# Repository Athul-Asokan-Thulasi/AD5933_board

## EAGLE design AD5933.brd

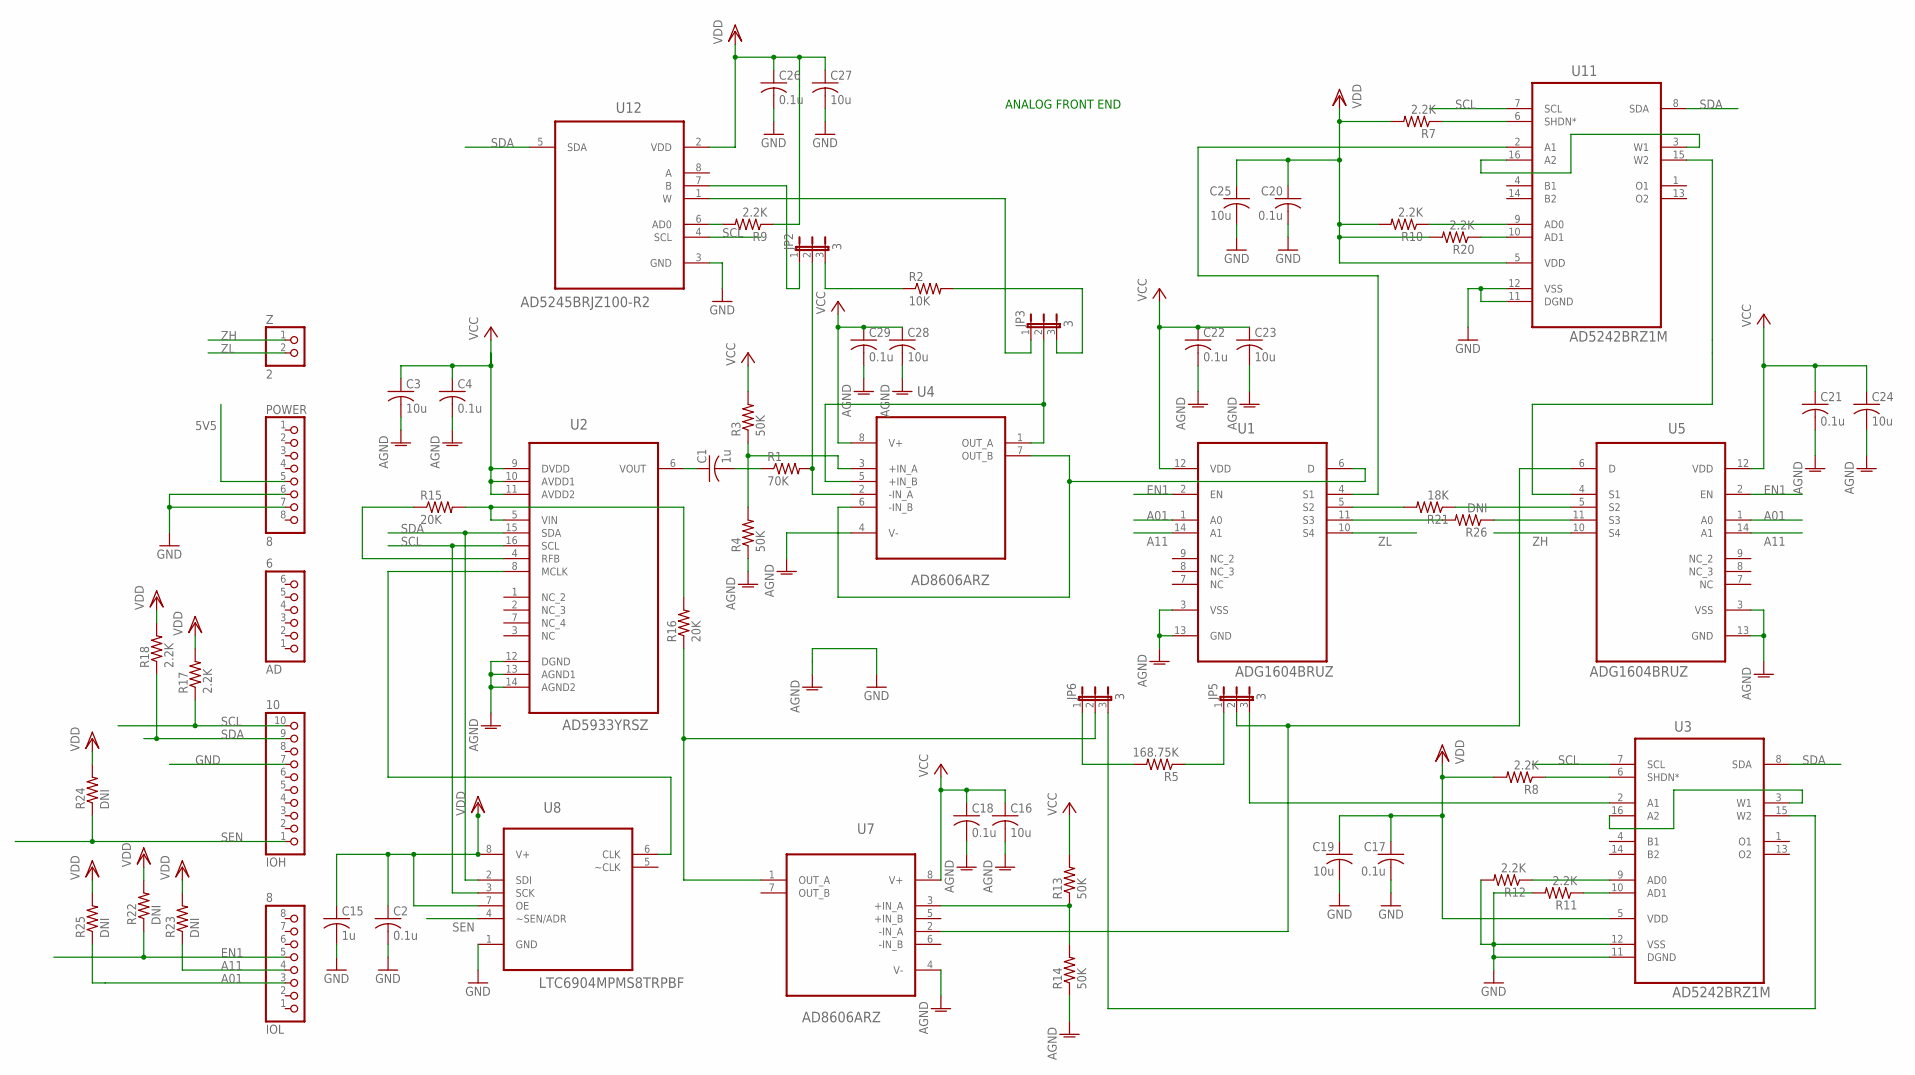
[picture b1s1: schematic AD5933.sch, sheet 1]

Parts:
AD: 6; 1X06
C1, C15: 1u; C0805
C2, C4, C17, C18, C20, C21, C22, C26, C29: 0.1u; C0805
C3, C16, C19, C23, C24, C25, C27, C28: 10u; C0805
IOH: 10; 1X10
IOL: 8; 1X08
JP2, JP3, JP5, JP6: 3; JP2
POWER: 8; 1X08
R1: 70K; M0805
R2: 10K; M0805
R3, R4, R13, R14: 50K; M0805
R5: 168.75K; M0805
R7, R8, R9, R10, R11, R12, R17, R18, R20: 2.2K; M0805
R15, R16: 20K; M0805
R21: 18K; M0805
R22, R23, R24, R25, R26: DNI; M0805
U1, U5: ADG1604BRUZ; SOP65P640X120-14N
U2: AD5933YRSZ; SOP65P640X120-16N
U3, U11: AD5242BRZ1M; SOIC127P600X175-16N
U4, U7: AD8606ARZ; SOIC127P600X175-8N
U8: LTC6904MPMS8TRPBF; SOP65P490X110-8N
U12: AD5245BRJZ100-R2; SOT65P280X145-8N
Z: 2; 1X02

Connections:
5V5: POWER.5; also elsewhere on the board
A01: IOL.3, R25.1, U1.1 (A0), U5.1 (A0)
A11: IOL.4, R23.1, U1.14 (A1), U5.14 (A1)
AGND: C3.2, C4.2, C16.2, C18.2, C21.2, C22.2, C23.2, C24.2, C28.2, C29.2, R4.1, R14.1, U1.3 (VSS), U1.13 (GND), U2.12 (DGND), U2.13 (AGND1), U2.14 (AGND2), U4.4 (V-), U5.3 (VSS), U5.13 (GND), U7.4 (V-); also elsewhere on the board
EN1: IOL.5, R22.1, U1.2 (EN), U5.2 (EN)
GND: C2.2, C15.2, C17.2, C19.2, C20.2, C25.2, C26.2, C27.2, IOH.7, POWER.6, POWER.7, R11.2, R12.2, U3.11 (DGND), U3.12 (VSS), U8.1 (GND), U11.11 (DGND), U11.12 (VSS), U12.3 (GND); also elsewhere on the board
unnamed: C1.1, U2.6 (VOUT)
unnamed: C1.2, R1.1
unnamed: JP5.1, R5.1
unnamed: R7.1, U11.6 (SHDN*)
unnamed: JP3.3, R2.2
unnamed: JP6.1, R5.2
unnamed: R8.1, U3.6 (SHDN*)
unnamed: JP2.3, R2.1
SCL: IOH.10, R17.1, U2.16 (SCL), U3.7 (SCL), U8.3 (SCK), U11.7 (SCL), U12.4 (SCL)
SDA: IOH.9, R18.1, U2.15 (SDA), U3.8 (SDA), U8.2 (SDI), U11.8 (SDA), U12.5 (SDA)
SEN: IOH.1, R24.1, U8.4 (~SEN/ADR)
U1_S1: U1.4 (S1), U11.2 (A1)
U1_S2: R21.2, U1.5 (S2)
U1_S3: R26.2, U1.11 (S3)
U2_MCLK: U2.8 (MCLK), U8.6 (CLK)
U2_RFB: R15.1, U2.4 (RFB)
U2_VIN: R15.2, R16.2, U2.5 (VIN)
U3_A1: JP5.3, U3.2 (A1)
U3_AD0: R12.1, U3.9 (AD0)
U3_AD1: R11.1, U3.10 (AD1)
U3_W1: U3.3 (W1), U3.16 (A2)
U3_W2: JP6.3, U3.15 (W2)
U4_INA++: R3.1, R4.2, U4.3 (+IN_A)
U4_INA--: JP2.2, R1.2, U4.2 (-IN_A)
U4_OUTA: JP3.2, U4.1 (OUT_A), U4.5 (+IN_B)
U4_OUTB: U1.6 (D), U4.6 (-IN_B), U4.7 (OUT_B)
U5_S2: R21.1, U5.5 (S2)
U5_S3: R26.1, U5.11 (S3)
U7_INA+: R13.1, R14.2, U7.3 (+IN_A)
U7_INA-: JP5.2, U5.6 (D), U7.2 (-IN_A)
U7_OUTA: JP6.2, R16.1, U7.1 (OUT_A)
U11_AD0: R10.1, U11.9 (AD0)
U11_AD1: R20.1, U11.10 (AD1)
U11_W1: U11.3 (W1), U11.16 (A2)
U11_W2: U5.4 (S1), U11.15 (W2)
U12_AD0: R9.2, U12.6 (AD0)
U12_B: JP2.1, U12.7 (B)
U12_W: JP3.1, U12.1 (W)
VCC: C3.1, C4.1, C16.1, C18.1, C21.1, C22.1, C23.1, C24.1, C28.1, C29.1, R3.2, R13.2, U1.12 (VDD), U2.9 (DVDD), U2.10 (AVDD1), U2.11 (AVDD2), U4.8 (V+), U5.12 (VDD), U7.8 (V+); also elsewhere on the board
VDD: C2.1, C15.1, C17.1, C19.1, C20.1, C25.1, C26.1, C27.1, R7.2, R8.2, R9.1, R10.2, R17.2, R18.2, R20.2, R22.2, R23.2, R24.2, R25.2, U3.5 (VDD), U8.7 (OE), U8.8 (V+), U11.5 (VDD), U12.2 (VDD); also elsewhere on the board
ZH: U5.10 (S4), Z.1
ZL: U1.10 (S4), Z.2

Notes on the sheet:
ANALOG FRONT END

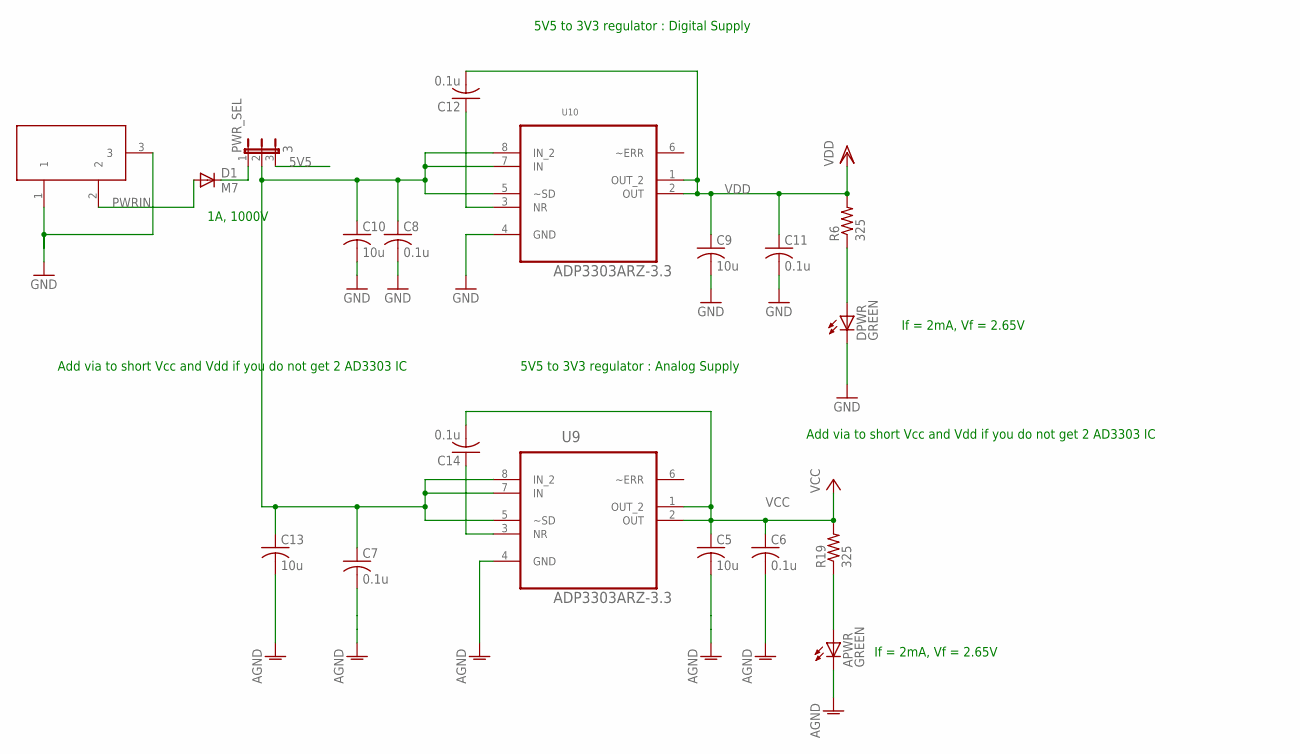
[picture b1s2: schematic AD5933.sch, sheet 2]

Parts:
APWR: GREEN; CHIP-LED0805
C5, C9, C10, C13: 10u; C0805
C6, C7, C8, C11, C12, C14: 0.1u; C0805
D1: M7; SMB
DPWR: GREEN; CHIP-LED0805
PWR_SEL: 3; JP2
R6, R19: 325; M0805
U9, U10: ADP3303ARZ-3.3; SOIC127P600X175-8N
X1: DC21MMX; DC-21MM

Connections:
5V5: PWR_SEL.3; also elsewhere on the board
AGND: APWR.C, C5.2, C6.2, C7.2, C13.2, U9.4 (GND); also elsewhere on the board
GND: C8.2, C9.2, C10.2, C11.2, DPWR.C, U10.4 (GND), X1.1, X1.3; also elsewhere on the board
unnamed: C12.1, U10.3 (NR)
unnamed: DPWR.A, R6.1
unnamed: APWR.A, R19.1
unnamed: C14.1, U9.3 (NR)
PWRIN: D1.A, X1.2
PWR_INPUT: C7.1, C8.1, C10.1, C13.1, PWR_SEL.2, U9.5 (~SD), U9.7 (IN), U9.8 (IN_2), U10.5 (~SD), U10.7 (IN), U10.8 (IN_2)
VCC: C5.1, C6.1, C14.2, R19.2, U9.1 (OUT_2), U9.2 (OUT); also elsewhere on the board
VDD: C9.1, C11.1, C12.2, R6.2, U10.1 (OUT_2), U10.2 (OUT); also elsewhere on the board
VIN: D1.C, PWR_SEL.1

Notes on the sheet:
5V5 to 3V3 regulator : Digital Supply
5V5 to 3V3 regulator : Analog Supply
If = 2mA, Vf = 2.65V
1A, 1000V
Add via to short Vcc and Vdd if you do not get 2 AD3303 IC

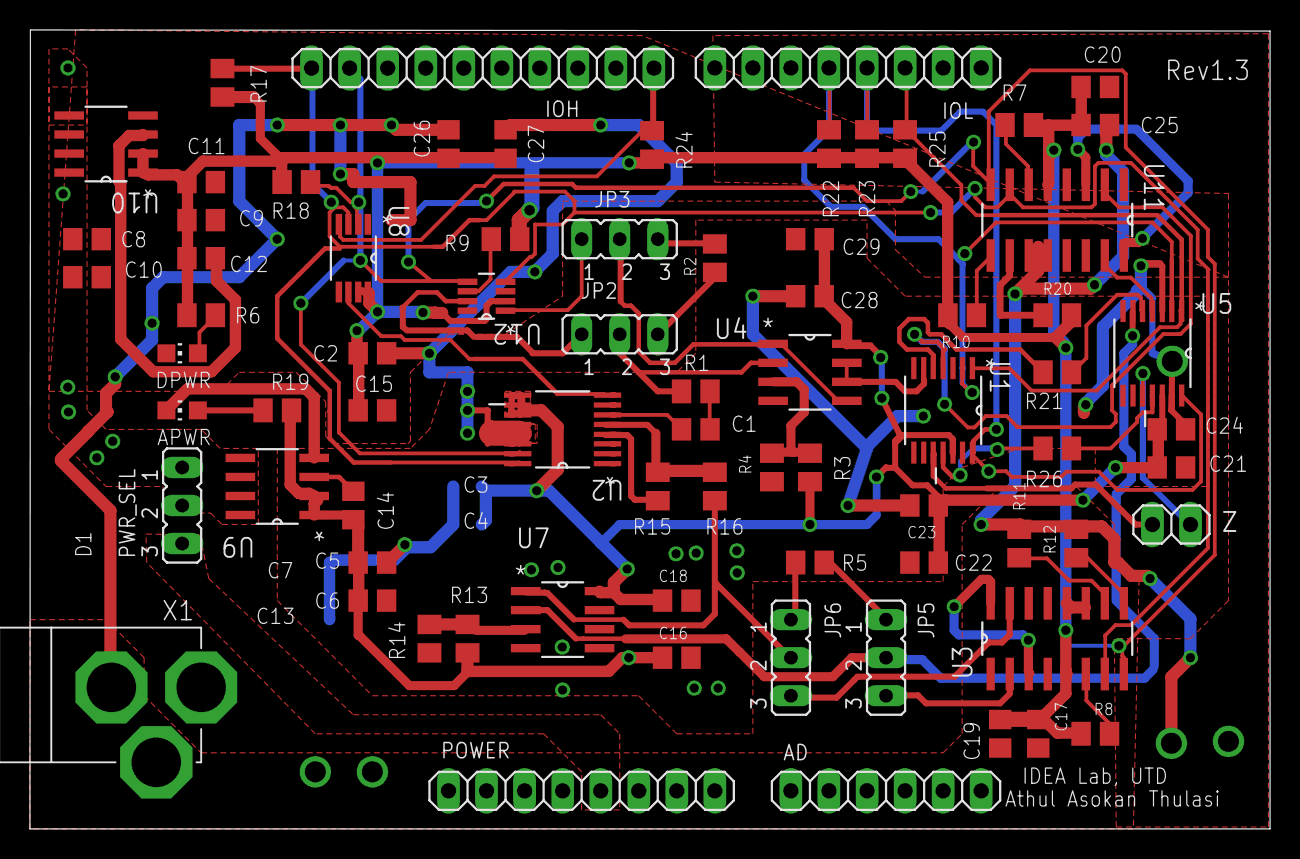
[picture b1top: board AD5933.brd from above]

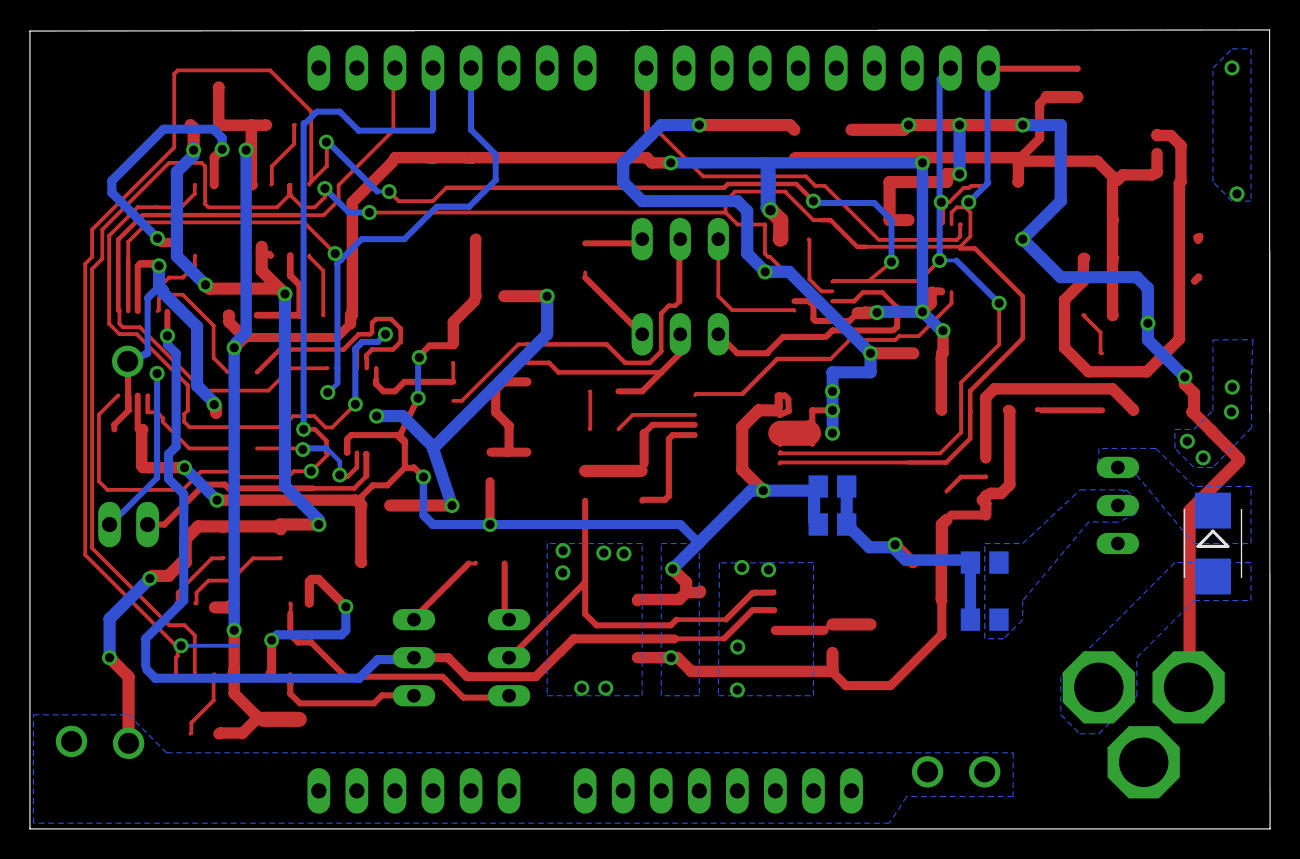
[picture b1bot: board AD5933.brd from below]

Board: 2 copper layers, 82.8 x 53.3 mm, 80 parts (5 on the bottom side), 55 nets.

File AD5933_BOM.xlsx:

Qty | Value | Device | Package | PACKAGE | MPN | Status | Order Site | Parts | Description
15 | 0.1u | C-USC0805 | C0805 |  |  | 10% ceramic - 50nos | Newark | C2, C4, C6, C7, C8, C11, C12, C14, C17, C18, C20, C21, C22, C26, C29 | CAPACITOR, American symbol
1 | 10 | PINHD-1X10 | 1X10 |  |  | 3 nos | Newark | IOH | PIN HEADER
1 | 10K | R-US_M0805 | M0805 |  |  | 0.1% -4nos | Newark | R2 | RESISTOR, American symbol
12 | 10u | C-USC0805 | C0805 |  |  | 10% cearamic - 35 nos, 10 tantalum | Newark | C3, C5, C9, C10, C13, C16, C19, C23, C24, C25, C27, C28 | CAPACITOR, American symbol
1 | 168.75K | R-US_M0805 | M0805 |  |  | 0.1% 169k 10nos | Newark | R5 | RESISTOR, American symbol
1 | 18K | R-US_M0805 | M0805 |  |  | 0.1% -4nos | Newark | R21 | RESISTOR, American symbol
2 | 1u | C-USC0805 | C0805 |  |  | 5% ceramic | Newark | C1, C15 | CAPACITOR, American symbol
1 | 2 | PINHD-1X2 | 1X02 |  |  | 3nos | Newark | JP1 | PIN HEADER
9 | 2.2K | R-US_M0805 | M0805 |  |  | 1% 40 nos | Newark | R7, R8, R9, R10, R11, R12, R17, R18, R20 | RESISTOR, American symbol
2 | 20K | R-US_M0805 | M0805 |  |  | 0.1% 8nos | Newark | R15, R16 | RESISTOR, American symbol
5 | 3 | JP2E | JP2 |  |  | 16 nos | Newark | JP2, JP3, JP4, JP5, JP6 | JUMPER
2 | 325 | R-US_M0805 | M0805 |  |  | 1% 316 10 nos, 1% 150ohm 10nos | Newark | R6, R19 | RESISTOR, American symbol
4 | 50K | R-US_M0805 | M0805 |  |  | 0.1% 14nos 51K | Newark | R3, R4, R13, R14 | RESISTOR, American symbol
1 | 6 | PINHD-1X6 | 1X06 |  |  | 3 nos | Newark | AD | PIN HEADER
1 | 70K | R-US_M0805 | M0805 |  |  | 69.8K 0.1% 5nos | Newark | R1 | RESISTOR, American symbol
2 | 8 | PINHD-1X8 | 1X08 |  |  | 6 nos of 10 pin | Newark | IOL, POWER | PIN HEADER
2 | AD5242BRZ1M | AD5242BRZ1M | SOIC127P600X175-16N | 16-Lead SOIC_N | AD5242BRZ1M | sampled 2 abhishek |  | U3, U11 | I2C Compatible Digital Potentiometer
1 | AD5245BRJZ100-R2 | AD5245BRJZ100-R2 | SOT65P280X145-8N | SOT-23-8 | AD5245BRJZ100-R2 | sampled 2 |  | U12 | 256-Position I2C-Compatible Digital Potentiometer
1 | AD5933YRSZ | AD5933YRSZ | SOP65P640X120-16N | TSSOP-16 | AD5933YRSZ | have 4 |  | U2 | 1 MSPS, 12-Bit Impedance Converter, Network Analyzer
2 | AD8606ARZ | AD8606ARZ | SOIC127P600X175-8N | SOIC-8 | AD8606ARZ | sampled 2, sampled 2 devang |  | U4, U7 | Precision, Low Noise, CMOS, Rail-to-Rail, Input/Output Operational Amplifiers
2 | ADG1604BRUZ | ADG1604BRUZ | SOP65P640X120-14N | TSSOP-14 | ADG1604BRUZ | sampled 2, sampled 2 devang |  | U1, U5 | 1 Ù Typical On Resistance, ±5 V,+12 V, +5 V, and +3.3 V, 4:1 Multiplexer
2 | ADP3303ARZ-3.3 | ADP3303ARZ-3.3 | SOIC127P600X175-8N | SOIC-8 | ADP3303ARZ-3.3 | 1 sampled,sampled 2 abhishek |  | U9, U10 | Linear Regulator
1 | ARDUINO_MEGA2560 | ARDUINO_MEGA2560 | ARDUINO_MEGA2560 |  |  | arealdy have one |  | PCB1 | Device for representing an Arduino Mega 2560 board
1 | DC21MMX | DC21MMX | DC-21MM |  |  | 2nos | Digikey | X1
2 | GREEN | LEDCHIP-LED0805 | CHIP-LED0805 |  |  | 7nos 2mA, 2.65vf | Digikey | ANALOG_PWR, DIGITAL_PWR | LED
1 | LTC6904MPMS8TRPBF | LTC6904MPMS8TRPBF | SOP65P490X110-8N | MSOP-8 | LTC6904MPMS8#TRPBF | 2 sampled |  | U8 | 1kHz 68MHz Serial Port Programmable Oscillator
1 | M7 | DIODE-SMB | SMB |  |  |  | Digikey | D1 | DIODE

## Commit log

2016-10-13 Initial Schematic
2016-10-13 Seperate VDD,VCC(Analog) added bypass capacitors to all chips
2016-10-14 Add digipots
2016-10-14 Review DRC error
2016-10-14 Move analog muxes to analog power domain
2016-10-14 Replace IC from old libray name to new library name(same library)
2016-10-15 Add jumper connections to arduino mega
2016-10-19 placed in shield area
2016-10-19 Manual routing, add ground planes
2016-10-19 Complete Routing,Semi Automatic
2016-10-20 complete DRC in layout
2016-10-20 Minor modifications
2016-10-20 Modify top silk screen, estimate wirelength
2016-10-20 CIMD version 1
2016-10-20 Modified Silk screen
2016-10-20 Silk screen modification 2
2016-11-11 Fix ad8606 wiring bug rev 1.1
2016-11-11 Increase AD5933 pad length
2016-11-30 Fixed ad5242 open ckt bug, rev 1.2
2016-11-30 fix ad5245 address to 0x2d to remove iic bus conflict with ad5242-u3
